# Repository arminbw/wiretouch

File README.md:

# WireTouch

WireTouch is an open multi-touch tracker based on mutual (projected) capacitance sensing. It was designed and built to foster research in the field of human-computer interaction. Please visit http://www.arminbwagner.com/wiretouch for demos and background information. You may also want to have a look at this paper:

.

The authors are currently not working on further updates. Feel free to fork the project and extend it as you see fit.

## Building
### WireTouch Firmware
1. The heart of the WireTouch hardware is an ATmega328P microcontroller equipped with an Arduino bootloader. To upload the WireTouch firmware, connect the mainboard with your computer. Use an USB to serial UART FTDI 5V cable.

2. Open **hardware/v1.3/firmware/firmware.ino** in the [Arduino IDE](http://arduino.cc/en/Main/Software). Select **Tools>Board>Arduino UNO** and the correct port. **Upload the Arduino sketch.**

Please note: The patched FTDI driver is not working in the latest version of OS X. Please skip step 3 and just use the default (and unfortunately slower) standard Apple FTDI driver. 

~~3. Install the virtual com port [FTDI driver](http://www.ftdichip.com/Drivers/VCP.htm). You need to patch the FTDIUSBSerialDriver configuration to increase the symbol rate of the computer-mainboard connection (see [FTDI Application Note 120](http://www.ftdichip.com/Support/Documents/AppNotes/AN_120_Aliasing_VCP_Baud_Rates.pdf)). We prepared a little perl script for that. Run it as the superuser: ```sudo perl modify-ftdi-driver-settings.pl``` If you are running El Capitan (or a later Mac OS version) you will also have to deactivate the new system integrity protection (SIP) to make this work \(see [issue #1](https://github.com/arminbw/wiretouch/issues/1)\).~~

### WireTouch Monitor
1. Download [openFrameworks 0.8.4](https://github.com/openframeworks/openFrameworks).
2. Download the following openFrameworks addons and put them into your openFrameworks ```addons``` directory:.

  * [ofxCv](https://github.com/kylemcdonald/ofxCv)
  * [ofxUI](https://github.com/rezaali/ofxUI)
  * [ofxBlobsManager](https://github.com/peteruithoven/ofxBlobsManager)

3. Copy the wiretouch_monitor directory of this repository into your openFrameworks ```apps/myApps/``` directory.
4. We are currently using Xcode 7.3 on OSX 10.11.4 for development. Open the Xcode project. **Build it**.

Next to the openFrameworks addons we are also using several other 3rd-party libraries. You do not have to download them manually as they already reside inside the src/3rd-party directory (This list is just for future reference and to give credit).
* [cjson](https://github.com/DaveGamble/cJSON)
* [oscpack](http://code.google.com/p/oscpack)
* [TUIO C++ library](https://github.com/mkalten/TUIO11_CPP)

## License
WireTouch is free software: you can redistribute it and/or modify it under the terms of the GNU General Public License as published by the Free Software Foundation, either version 3 of the License, or (at your option) any later version.

A few of the included 3rd-party libraries are licensed under the GPL-compatible MIT license.

WireTouch is distributed in the hope that it will be useful, but WITHOUT ANY WARRANTY; without even the implied warranty of merchantability or fitness for a particular purpose. See the [GNU General Public License](http://www.gnu.org/licenses) for more details.

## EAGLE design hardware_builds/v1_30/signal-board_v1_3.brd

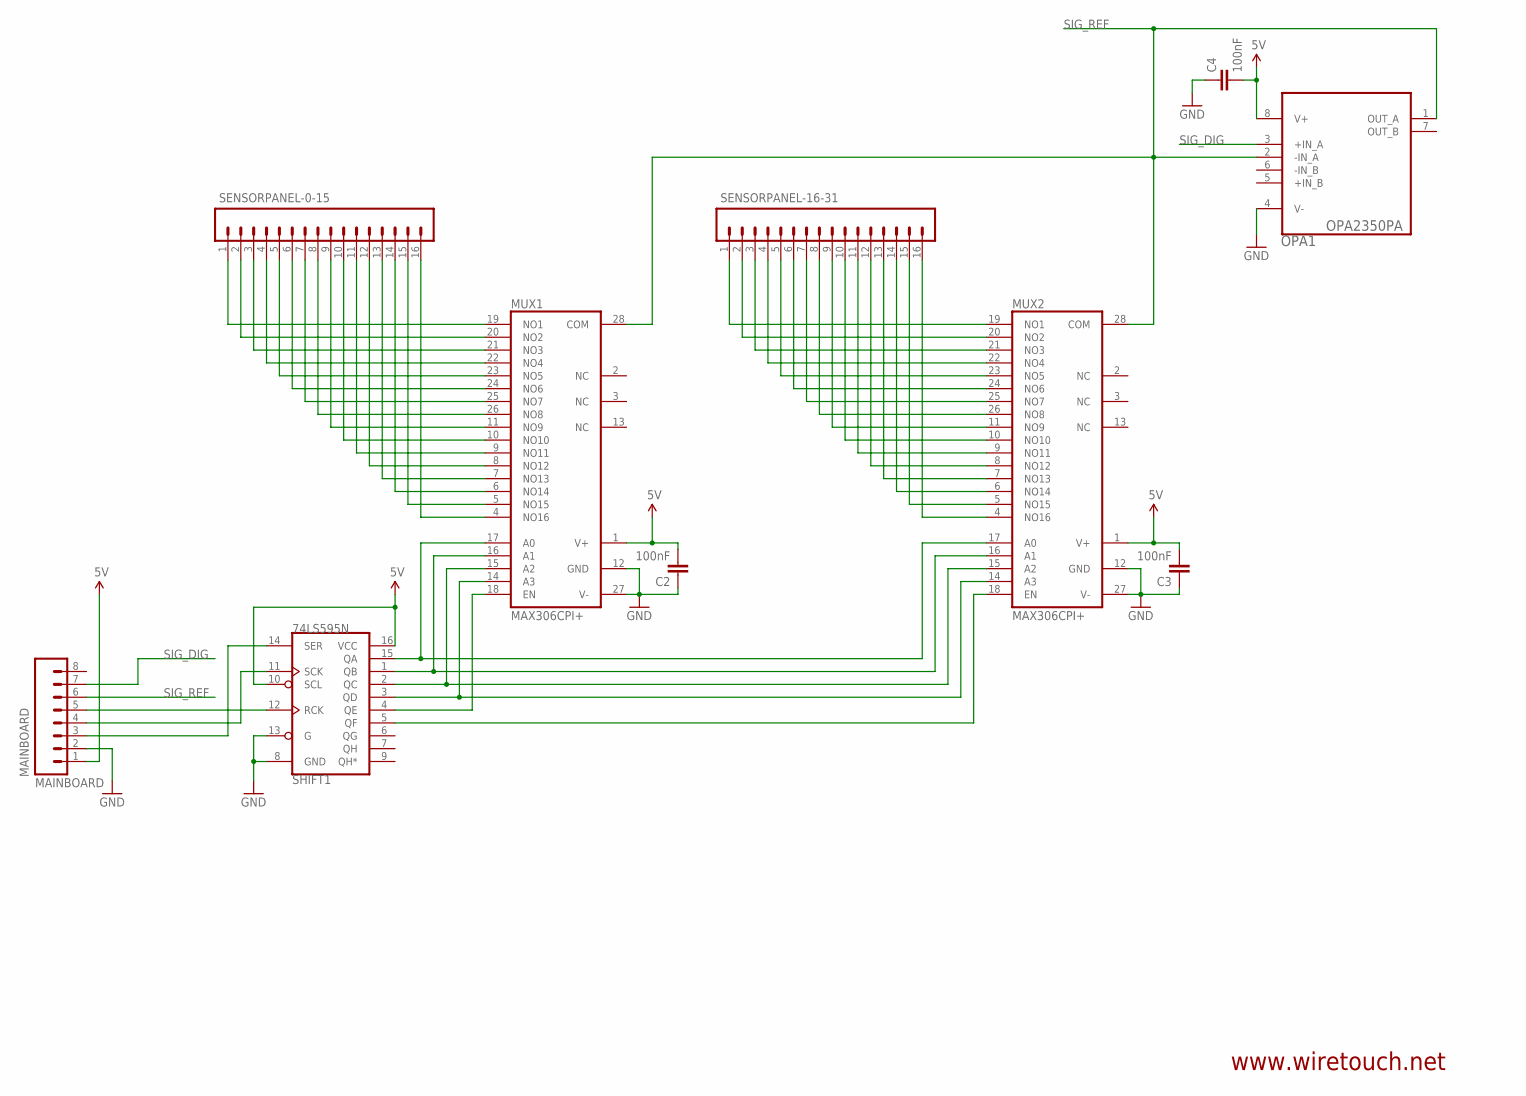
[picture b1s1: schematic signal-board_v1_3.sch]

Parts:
C2, C3, C4: 100nF; CAP-PTH-SMALL
MAINBOARD: MAINBOARD; 1X08_LONGPADS
MUX1, MUX2: MAX306CPI+; DIL28-6
OPA1: OPA2350PA; DIP254P762X508-8
SENSORPANEL-0-15, SENSORPANEL-16-31: M16LOCK_LONGPADS; 1X16_LOCK_LONGPADS
SHIFT1: 74LS595N; DIL16

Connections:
5V: C2.2, C3.2, C4.2, MAINBOARD.1, MUX1.1 (V+), MUX2.1 (V+), OPA1.8 (V+), SHIFT1.10 (SCL), SHIFT1.16 (VCC)
GND: C2.1, C3.1, C4.1, MAINBOARD.2, MUX1.12 (GND), MUX1.27 (V-), MUX2.12 (GND), MUX2.27 (V-), OPA1.4 (V-), SHIFT1.8 (GND), SHIFT1.13 (G)
unnamed: MUX1.19 (NO1), SENSORPANEL-0-15.1
unnamed: MUX1.21 (NO3), SENSORPANEL-0-15.3
unnamed: MUX1.23 (NO5), SENSORPANEL-0-15.5
unnamed: MUX1.25 (NO7), SENSORPANEL-0-15.7
unnamed: MUX1.11 (NO9), SENSORPANEL-0-15.9
unnamed: MUX1.9 (NO11), SENSORPANEL-0-15.11
unnamed: MUX1.7 (NO13), SENSORPANEL-0-15.13
unnamed: MUX1.5 (NO15), SENSORPANEL-0-15.15
unnamed: MUX2.19 (NO1), SENSORPANEL-16-31.1
unnamed: MUX2.21 (NO3), SENSORPANEL-16-31.3
unnamed: MUX2.23 (NO5), SENSORPANEL-16-31.5
unnamed: MUX2.25 (NO7), SENSORPANEL-16-31.7
unnamed: MUX2.11 (NO9), SENSORPANEL-16-31.9
unnamed: MUX2.9 (NO11), SENSORPANEL-16-31.11
unnamed: MUX2.7 (NO13), SENSORPANEL-16-31.13
unnamed: MUX2.5 (NO15), SENSORPANEL-16-31.15
unnamed: MUX1.20 (NO2), SENSORPANEL-0-15.2
unnamed: MUX1.22 (NO4), SENSORPANEL-0-15.4
unnamed: MUX1.24 (NO6), SENSORPANEL-0-15.6
unnamed: MUX1.26 (NO8), SENSORPANEL-0-15.8
unnamed: MUX1.10 (NO10), SENSORPANEL-0-15.10
unnamed: MUX1.8 (NO12), SENSORPANEL-0-15.12
unnamed: MUX1.6 (NO14), SENSORPANEL-0-15.14
unnamed: MUX1.4 (NO16), SENSORPANEL-0-15.16
unnamed: MUX2.20 (NO2), SENSORPANEL-16-31.2
unnamed: MUX1.16 (A1), MUX2.16 (A1), SHIFT1.1 (QB)
unnamed: MUX1.17 (A0), MUX2.17 (A0), SHIFT1.15 (QA)
unnamed: MUX1.15 (A2), MUX2.15 (A2), SHIFT1.2 (QC)
unnamed: MUX2.22 (NO4), SENSORPANEL-16-31.4
unnamed: MAINBOARD.3, SHIFT1.14 (SER)
unnamed: MUX1.18 (EN), SHIFT1.4 (QE)
unnamed: MUX2.18 (EN), SHIFT1.5 (QF)
unnamed: MAINBOARD.4, SHIFT1.11 (SCK)
unnamed: MUX1.14 (A3), MUX2.14 (A3), SHIFT1.3 (QD)
unnamed: MAINBOARD.5, SHIFT1.12 (RCK)
unnamed: MUX2.24 (NO6), SENSORPANEL-16-31.6
unnamed: MUX2.26 (NO8), SENSORPANEL-16-31.8
unnamed: MUX2.10 (NO10), SENSORPANEL-16-31.10
unnamed: MUX2.8 (NO12), SENSORPANEL-16-31.12
unnamed: MUX2.6 (NO14), SENSORPANEL-16-31.14
unnamed: MUX2.4 (NO16), SENSORPANEL-16-31.16
SIG_DIG: MAINBOARD.7, OPA1.3 (+IN_A)
SIG_REF: MAINBOARD.6, MUX1.28 (COM), MUX2.28 (COM), OPA1.1 (OUT_A), OPA1.2 (-IN_A)

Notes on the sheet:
www.wiretouch.net

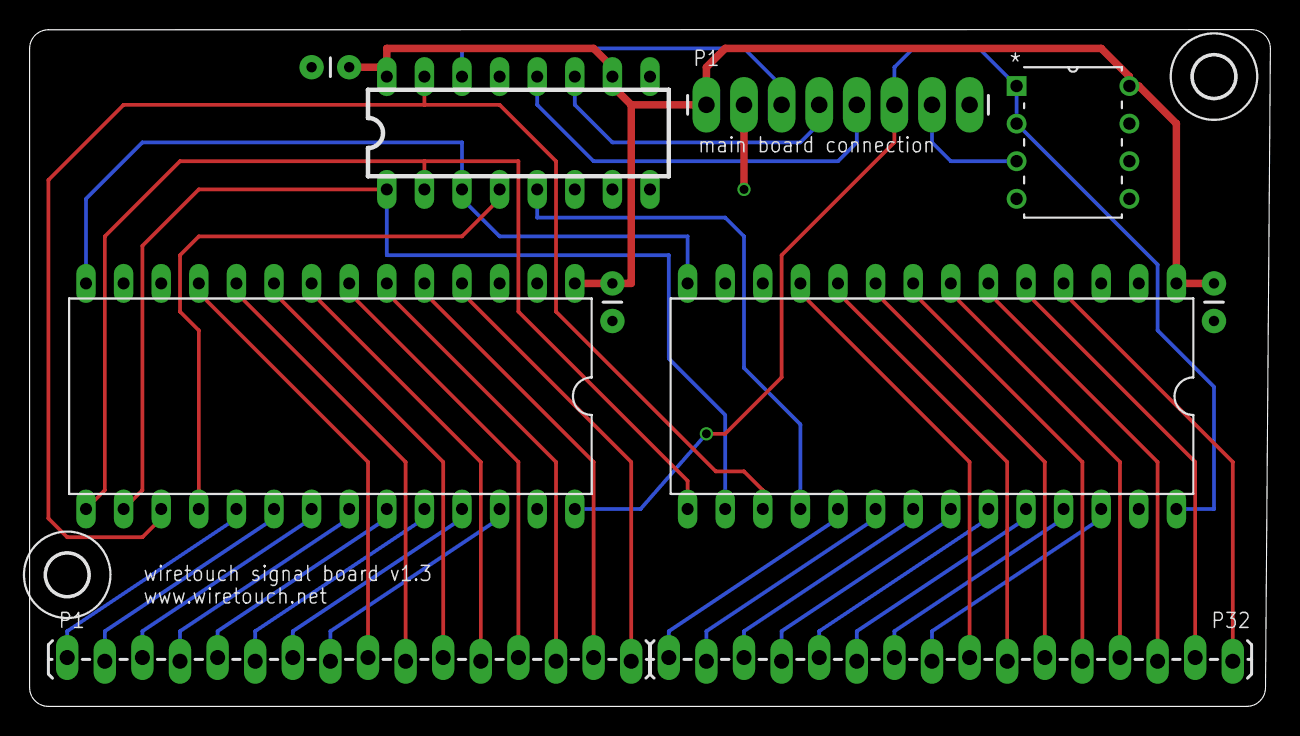
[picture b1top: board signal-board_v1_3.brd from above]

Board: 2 copper layers, 83.8 x 45.7 mm, 12 parts (0 on the bottom side), 45 nets.

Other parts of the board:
U$6, U$7: 2,8

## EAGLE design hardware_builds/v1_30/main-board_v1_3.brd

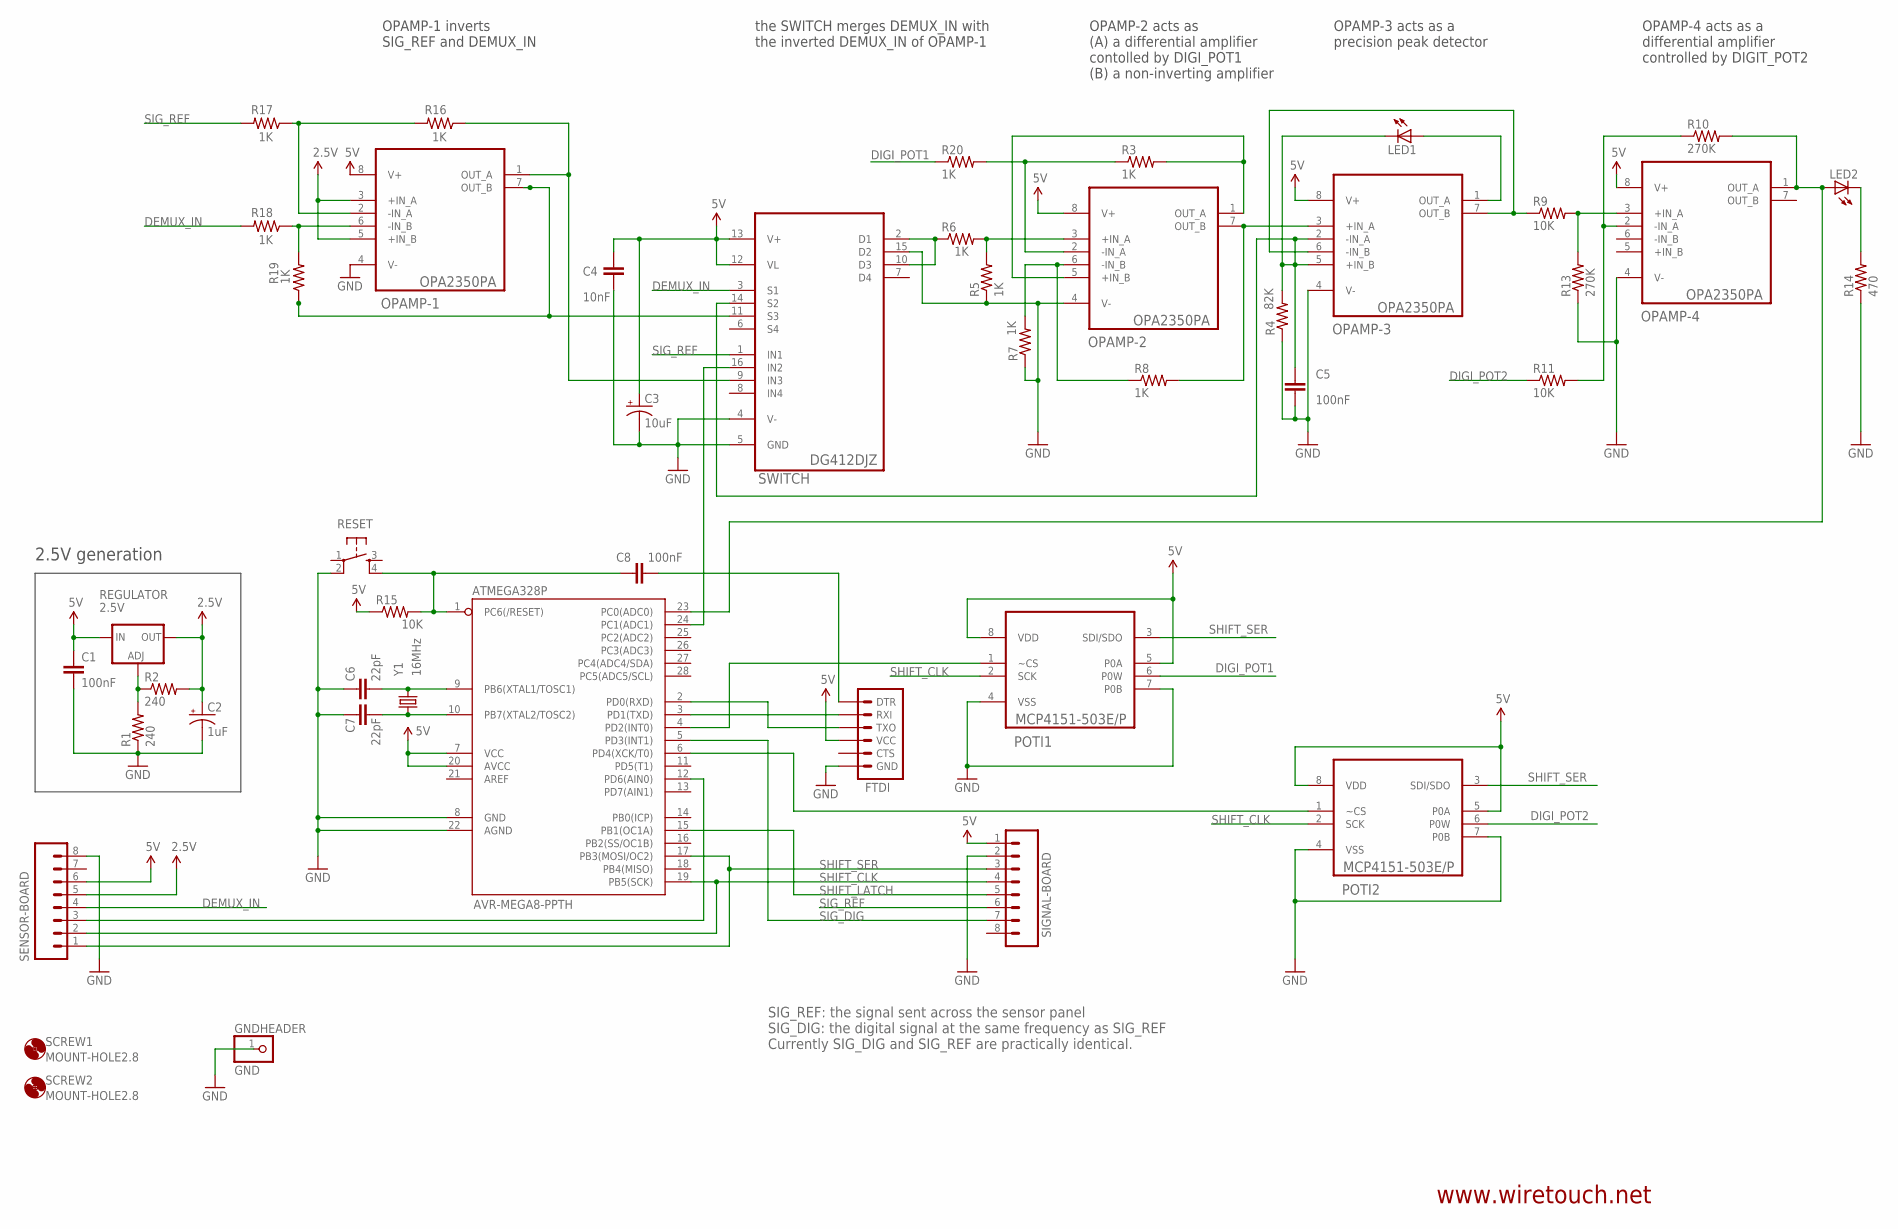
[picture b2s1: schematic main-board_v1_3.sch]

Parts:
ATMEGA328P: AVR-MEGA8-PPTH; DIL28-3
C1, C5: 100nF; CAP-PTH-SMALL
C2: 1uF; CPOL-RADIAL-10UF-25V
C3: 10uF; CPOL-RADIAL-10UF-25V
C4: 10nF; CAP-PTH-SMALL
C6, C7: 22pF; CAP-PTH-SMALL2
C8: 100nF; CAP-PTH-SMALL2
FTDI: ARDUINO_SERIAL_PROGRAMLONGPADS; 1X06_LONGPADS
GNDHEADER: GND; 1X01
LED1: LED3MM
LED2: LED5MM
OPAMP-1, OPAMP-2, OPAMP-3, OPAMP-4: OPA2350PA; DIP254P762X508-8
POTI1, POTI2: MCP4151-503E/P; DIP254P762X533-8
R1, R2: 240; AXIAL-0.3
R3, R5, R6, R7, R8, R16, R17, R18, R19, R20: 1K; AXIAL-0.3
R4: 82K; AXIAL-0.3
R9, R11, R15: 10K; AXIAL-0.3
R10, R13: 270K; AXIAL-0.3
R14: 470; AXIAL-0.3
REGULATOR: 2.5V; TO220-ADJ
RESET: Omron B3F momentary on switch; TACTILE-PTH
SCREW1, SCREW2: MOUNT-HOLE2.8; 2,8
SENSOR-BOARD: M08LONGPADS; 1X08_LONGPADS
SIGNAL-BOARD: M08LONGPADS; 1X08_LONGPADS
SWITCH: DG412DJZ; DIP254P762X533-16
Y1: 16MHz; HC49US

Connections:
2.8V: C2.1 (+), OPAMP-1.3 (+IN_A), OPAMP-1.5 (+IN_B), R2.P$2 (2), REGULATOR.OUT, SENSOR-BOARD.5
5V: ATMEGA328P.7 (VCC), ATMEGA328P.20 (AVCC), C1.1, C3.1 (+), C4.1, FTDI.4 (VCC), OPAMP-1.8 (V+), OPAMP-2.8 (V+), OPAMP-3.8 (V+), OPAMP-4.8 (V+), POTI1.5 (P0A), POTI1.8 (VDD), POTI2.5 (P0A), POTI2.8 (VDD), R15.P$1 (1), REGULATOR.IN, SENSOR-BOARD.6, SIGNAL-BOARD.1, SWITCH.12 (VL), SWITCH.13 (V+)
DEMUX_IN: R18.P$2 (2), SENSOR-BOARD.4, SWITCH.3 (S1)
DIGI_POT1: POTI1.6 (P0W), R20.P$1 (1)
DIGI_POT2: POTI2.6 (P0W), R11.P$1 (1)
GND: ATMEGA328P.8 (GND), ATMEGA328P.22 (AGND), C1.2, C2.2 (-), C3.2 (-), C4.2, C5.2, C6.1, C7.1, FTDI.6 (GND), GNDHEADER.1, OPAMP-1.4 (V-), OPAMP-2.4 (V-), OPAMP-3.4 (V-), OPAMP-4.4 (V-), POTI1.4 (VSS), POTI1.7 (P0B), POTI2.4 (VSS), POTI2.7 (P0B), R1.P$1 (1), R4.P$1 (1), R5.P$1 (1), R7.P$1 (1), R13.P$1 (1), R14.P$1 (1), RESET.2, SENSOR-BOARD.8, SIGNAL-BOARD.2, SWITCH.4 (V-), SWITCH.5 (GND), SWITCH.15 (D2)
unnamed: R6.P$1 (1), SWITCH.2 (D1), SWITCH.10 (D3)
unnamed: OPAMP-2.1 (OUT_A), OPAMP-2.5 (+IN_B), R3.P$2 (2)
unnamed: R1.P$2 (2), R2.P$1 (1), REGULATOR.ADJ
unnamed: OPAMP-2.2 (-IN_A), R3.P$1 (1), R20.P$2 (2)
unnamed: OPAMP-2.3 (+IN_A), R5.P$2 (2), R6.P$2 (2)
unnamed: OPAMP-2.6 (-IN_B), R7.P$2 (2), R8.P$1 (1)
unnamed: OPAMP-4.2 (-IN_A), R10.P$1 (1), R11.P$2 (2)
unnamed: ATMEGA328P.24 (PC1(ADC1)), SWITCH.16 (IN2)
unnamed: LED1.A, OPAMP-3.1 (OUT_A)
unnamed: OPAMP-2.7 (OUT_B), OPAMP-3.3 (+IN_A), R8.P$2 (2)
unnamed: C5.1, LED1.K (C), OPAMP-3.2 (-IN_A), OPAMP-3.5 (+IN_B), R4.P$2 (2), SWITCH.14 (S2)
unnamed: OPAMP-3.6 (-IN_B), OPAMP-3.7 (OUT_B), R9.P$1 (1)
unnamed: OPAMP-4.3 (+IN_A), R9.P$2 (2), R13.P$2 (2)
unnamed: ATMEGA328P.23 (PC0(ADC0)), LED2.A, OPAMP-4.1 (OUT_A), R10.P$2 (2)
unnamed: ATMEGA328P.6 (PD4(XCK/T0)), POTI2.1 (~CS)
unnamed: OPAMP-1.6 (-IN_B), R18.P$1 (1), R19.P$2 (2)
unnamed: LED2.K (C), R14.P$2 (2)
unnamed: ATMEGA328P.9 (PB6(XTAL1/TOSC1)), C6.2, Y1.2
unnamed: ATMEGA328P.10 (PB7(XTAL2/TOSC2)), C7.2, Y1.1
unnamed: ATMEGA328P.1 (PC6(/RESET)), C8.1, R15.P$2 (2), RESET.4
unnamed: ATMEGA328P.3 (PD1(TXD)), FTDI.2 (RXI)
unnamed: ATMEGA328P.2 (PD0(RXD)), FTDI.3 (TXO)
unnamed: C8.2, FTDI.1 (DTR)
unnamed: OPAMP-1.1 (OUT_A), R16.P$1 (1), SWITCH.9 (IN3)
unnamed: OPAMP-1.2 (-IN_A), R16.P$2 (2), R17.P$1 (1)
unnamed: OPAMP-1.7 (OUT_B), R19.P$1 (1), SWITCH.11 (S3)
unnamed: ATMEGA328P.4 (PD2(INT0)), POTI1.1 (~CS)
unnamed: ATMEGA328P.12 (PD6(AIN0)), SENSOR-BOARD.3
SHIFT_CLK: ATMEGA328P.19 (PB5(SCK)), POTI1.2 (SCK), POTI2.2 (SCK), SENSOR-BOARD.2, SIGNAL-BOARD.4
SHIFT_LATCH: ATMEGA328P.15 (PB1(OC1A)), SIGNAL-BOARD.5
SHIFT_SER: ATMEGA328P.17 (PB3(MOSI/OC2)), POTI1.3 (SDI/SDO), POTI2.3 (SDI/SDO), SENSOR-BOARD.1, SIGNAL-BOARD.3
SIG_DIG: ATMEGA328P.5 (PD3(INT1)), SIGNAL-BOARD.7
SIG_REF: R17.P$2 (2), SIGNAL-BOARD.6, SWITCH.1 (IN1)

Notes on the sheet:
2.5V generation
www.wiretouch.net
SIG_REF: the signal sent across the sensor panel SIG_DIG: the digital signal at the same frequency as SIG_REF Currently SIG_DIG and SIG_REF are practically identical.
OPAMP-3 acts as a precision peak detector
OPAMP-4 acts as a differential amplifier controlled by DIGIT_POT2
OPAMP-2 acts as (A) a differential amplifier contolled by DIGI_POT1 (B) a non-inverting amplifier
OPAMP-1 inverts SIG_REF and DEMUX_IN
the SWITCH merges DEMUX_IN with the inverted DEMUX_IN of OPAMP-1

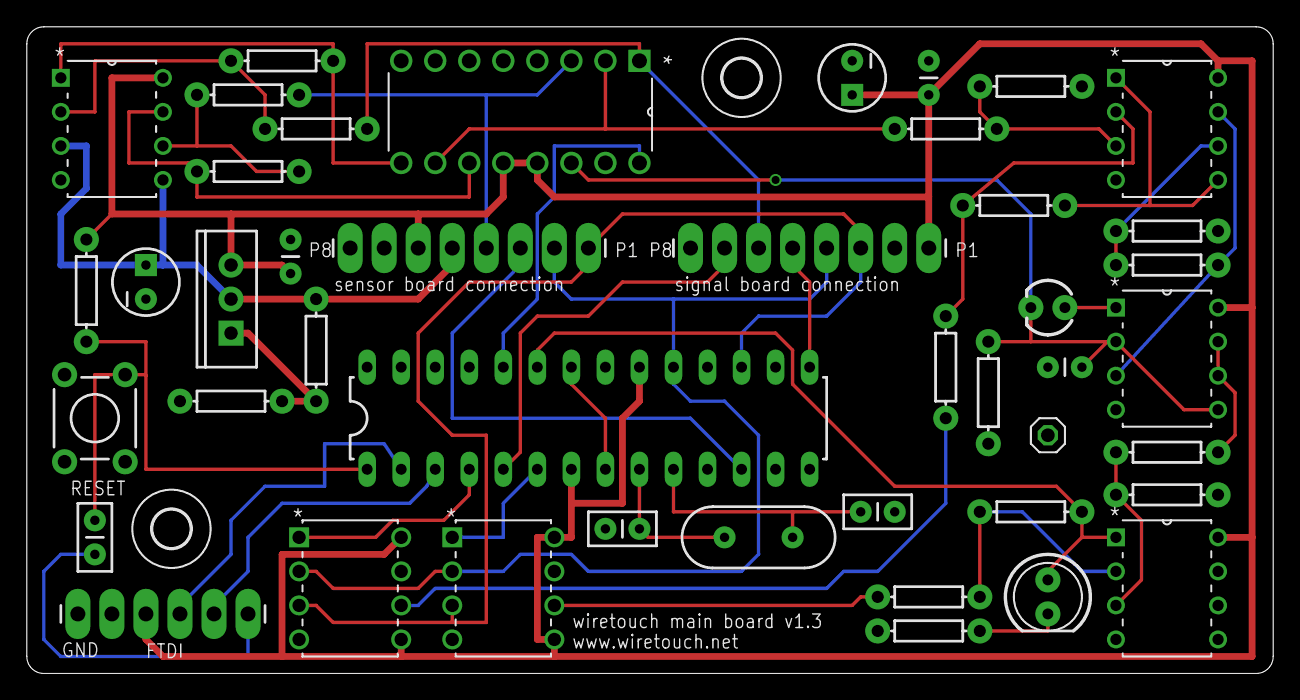
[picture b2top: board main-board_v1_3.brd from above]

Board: 2 copper layers, 93.0 x 48.3 mm, 46 parts (0 on the bottom side), 39 nets.

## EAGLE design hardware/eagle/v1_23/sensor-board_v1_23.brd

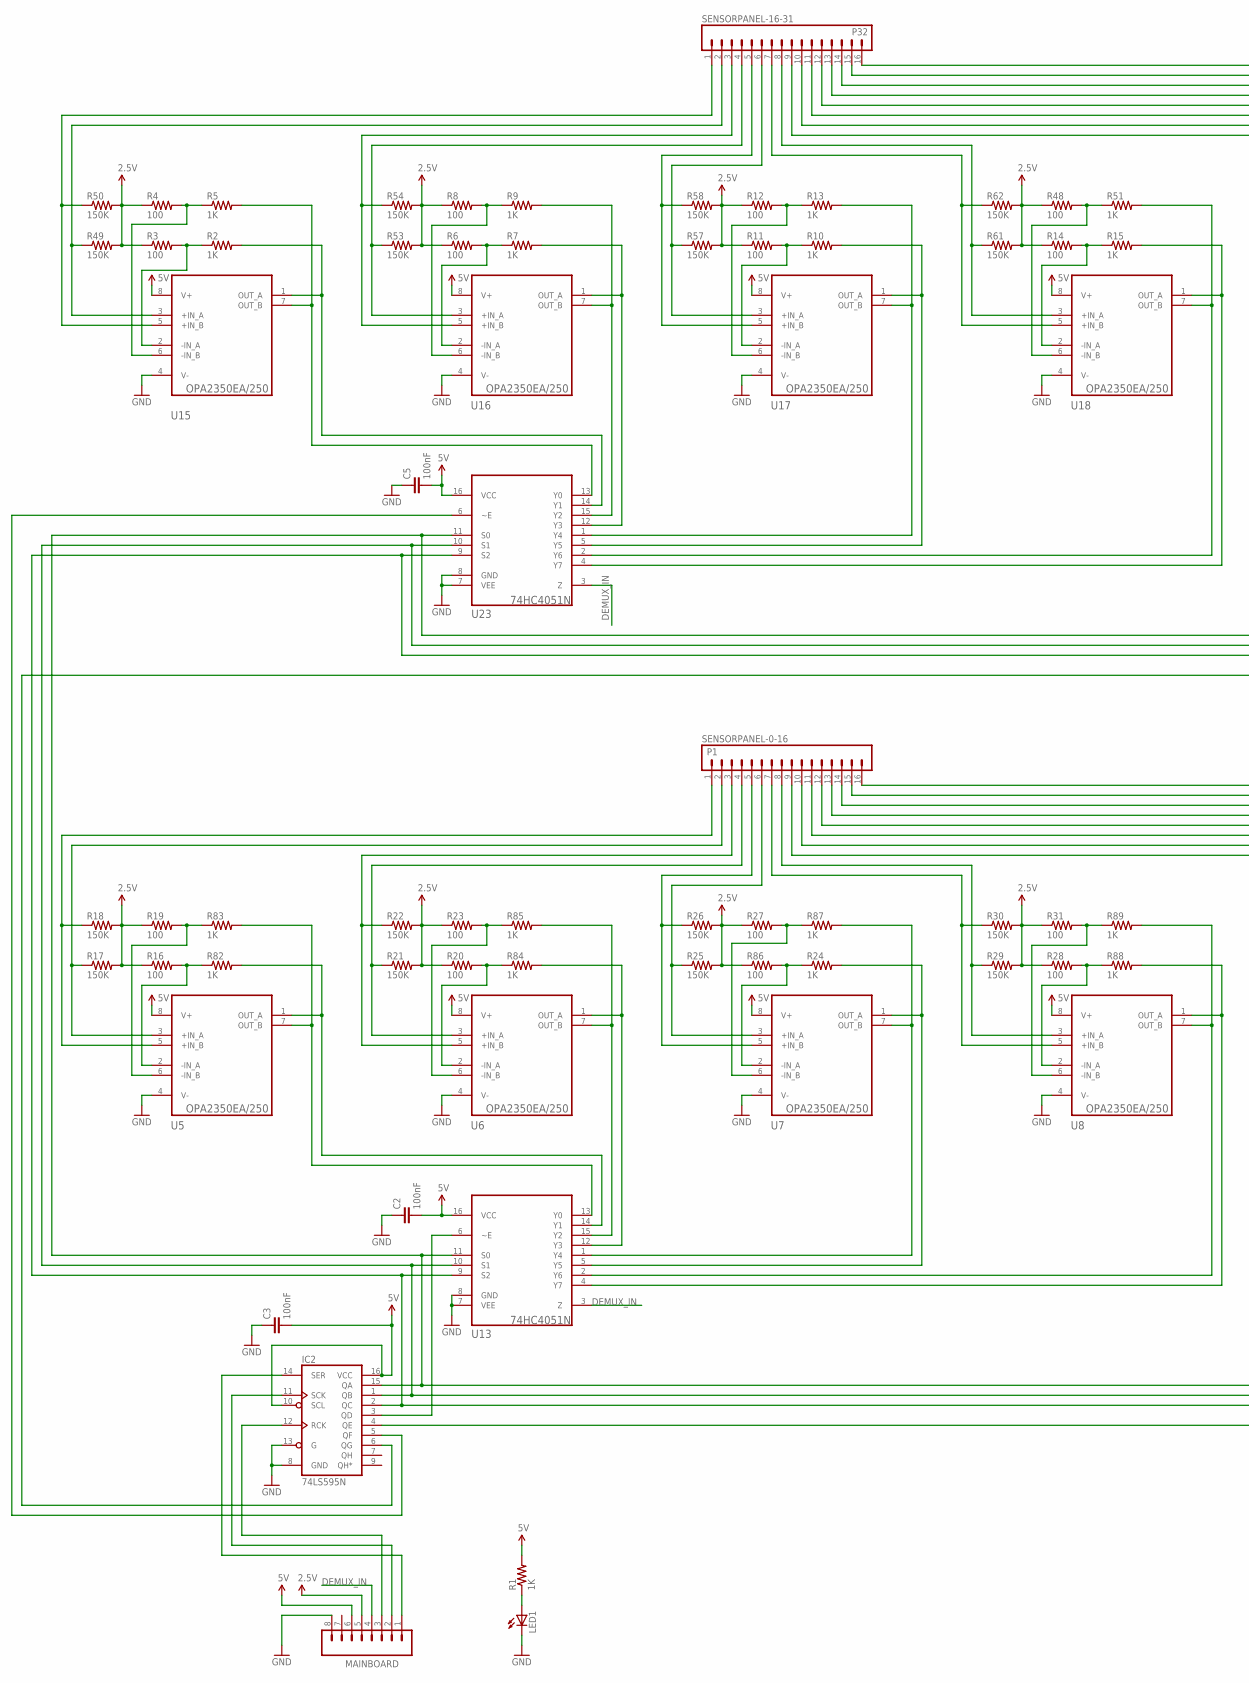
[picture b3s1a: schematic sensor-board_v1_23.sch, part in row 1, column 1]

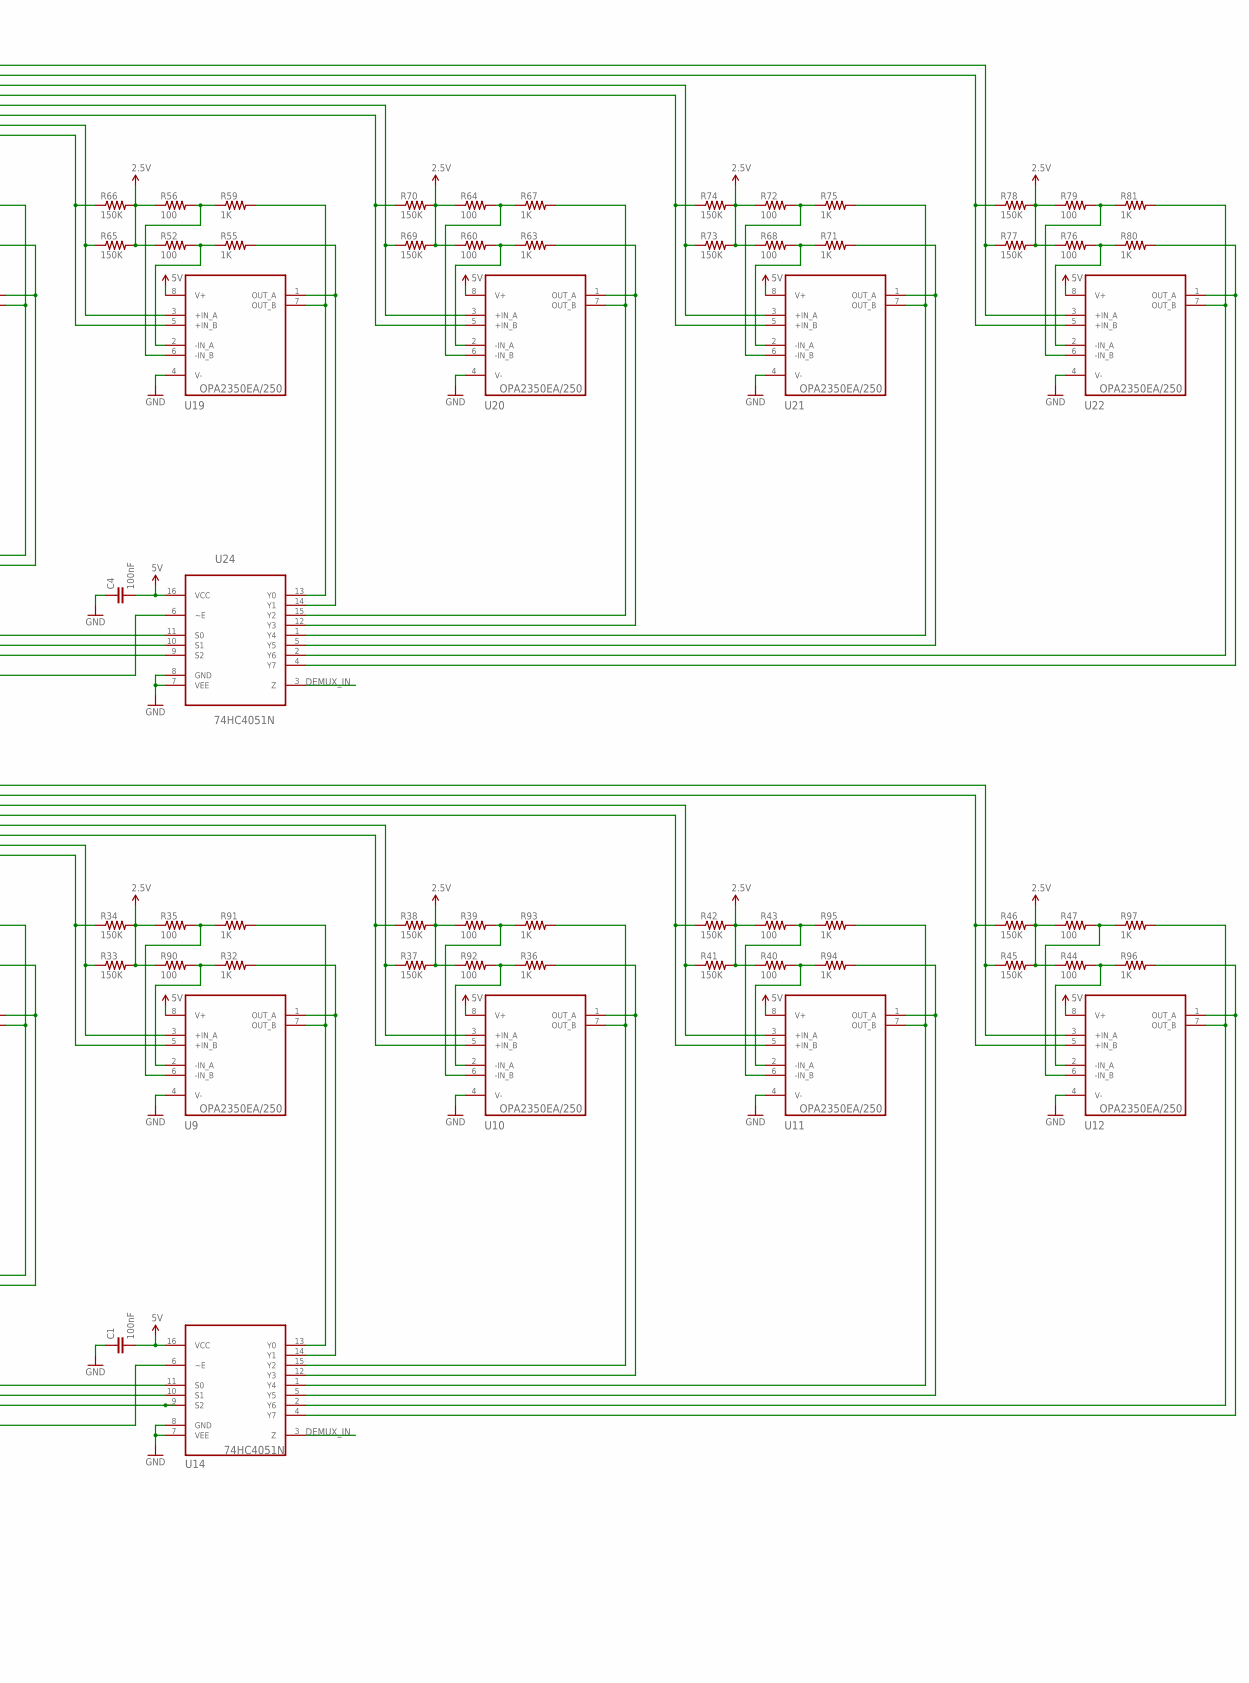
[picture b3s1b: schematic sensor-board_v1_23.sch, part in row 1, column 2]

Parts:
C1, C2, C3, C4, C5: 100nF; CAP-PTH-SMALL
IC2: 74LS595N; DIL16
LED1: LED0603; LED-0603
MAINBOARD: M08LONGPADS; 1X08_LONGPADS
R1, R2, R5, R7, R9, R10, R13, R15, R24, R32, R36, R51, R55, R59, R63, R67, R71, R75, R80, R81, R82, R83, R84, R85, R87, R88, R89, R91, R93, R94, R95, R96, R97: 1K; 0805
R3, R4, R6, R8, R11, R12, R14, R16, R19, R20, R23, R27, R28, R31, R35, R39, R40, R43, R44, R47, R48, R52, R56, R60, R64, R68, R72, R76, R79, R86, R90, R92: 100; 0805
R17, R18, R21, R22, R25, R26, R29, R30, R33, R34, R37, R38, R41, R42, R45, R46, R49, R50, R53, R54, R57, R58, R61, R62, R65, R66, R69, R70, R73, R74, R77, R78: 150K; 0805
SENSORPANEL-0-16: P1; 1X16_LOCK
SENSORPANEL-16-31: P32; 1X16_LOCK
U5, U6, U7, U8, U9, U10, U11, U12, U15, U16, U17, U18, U19, U20, U21, U22: OPA2350EA/250; SOP65P490X110-8N
U13, U14, U23, U24: 74HC4051N; DIP254P762X420-16

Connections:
2.8V: MAINBOARD.5, R3.1, R4.1, R6.1, R8.1, R11.1, R12.1, R14.1, R16.1, R17.2, R18.2, R19.1, R20.1, R21.2, R22.2, R23.1, R25.2, R26.2, R27.1, R28.1, R29.2, R30.2, R31.1, R33.2, R34.2, R35.1, R37.2, R38.2, R39.1, R40.1, R41.2, R42.2, R43.1, R44.1, R45.2, R46.2, R47.1, R48.1, R49.2, R50.2, R52.1, R53.2, R54.2, R56.1, R57.2, R58.2, R60.1, R61.2, R62.2, R64.1, R65.2, R66.2, R68.1, R69.2, R70.2, R72.1, R73.2, R74.2, R76.1, R77.2, R78.2, R79.1, R86.1, R90.1, R92.1
5V: C1.2, C2.2, C3.2, C4.2, C5.2, IC2.10 (SCL), IC2.16 (VCC), MAINBOARD.6, R1.2, U5.8 (V+), U6.8 (V+), U7.8 (V+), U8.8 (V+), U9.8 (V+), U10.8 (V+), U11.8 (V+), U12.8 (V+), U13.16 (VCC), U14.16 (VCC), U15.8 (V+), U16.8 (V+), U17.8 (V+), U18.8 (V+), U19.8 (V+), U20.8 (V+), U21.8 (V+), U22.8 (V+), U23.16 (VCC), U24.16 (VCC)
DEMUX_IN: MAINBOARD.4, U13.3 (Z), U14.3 (Z), U23.3 (Z), U24.3 (Z)
GND: C1.1, C2.1, C3.1, C4.1, C5.1, IC2.8 (GND), IC2.13 (G), LED1.C, MAINBOARD.8, U5.4 (V-), U6.4 (V-), U7.4 (V-), U8.4 (V-), U9.4 (V-), U10.4 (V-), U11.4 (V-), U12.4 (V-), U13.7 (VEE), U13.8 (GND), U14.7 (VEE), U14.8 (GND), U15.4 (V-), U16.4 (V-), U17.4 (V-), U18.4 (V-), U19.4 (V-), U20.4 (V-), U21.4 (V-), U22.4 (V-), U23.7 (VEE), U23.8 (GND), U24.7 (VEE), U24.8 (GND)
unnamed: LED1.A, R1.1
unnamed: R2.1, R3.2, U15.2 (-IN_A)
unnamed: R4.2, R5.1, U15.6 (-IN_B)
unnamed: R6.2, R7.1, U16.2 (-IN_A)
unnamed: R8.2, R9.1, U16.6 (-IN_B)
unnamed: R10.1, R11.2, U17.2 (-IN_A)
unnamed: R12.2, R13.1, U17.6 (-IN_B)
unnamed: R14.2, R15.1, U18.2 (-IN_A)
unnamed: R48.2, R51.1, U18.6 (-IN_B)
unnamed: R52.2, R55.1, U19.2 (-IN_A)
unnamed: R56.2, R59.1, U19.6 (-IN_B)
unnamed: R60.2, R63.1, U20.2 (-IN_A)
unnamed: R64.2, R67.1, U20.6 (-IN_B)
unnamed: R68.2, R71.1, U21.2 (-IN_A)
unnamed: R72.2, R75.1, U21.6 (-IN_B)
unnamed: R76.2, R80.1, U22.2 (-IN_A)
unnamed: R79.2, R81.1, U22.6 (-IN_B)
unnamed: R16.2, R82.1, U5.2 (-IN_A)
unnamed: R19.2, R83.1, U5.6 (-IN_B)
unnamed: R20.2, R84.1, U6.2 (-IN_A)
unnamed: R23.2, R85.1, U6.6 (-IN_B)
unnamed: R24.1, R86.2, U7.2 (-IN_A)
unnamed: R27.2, R87.1, U7.6 (-IN_B)
unnamed: R82.2, U5.1 (OUT_A), U13.14 (Y1)
unnamed: R83.2, U5.7 (OUT_B), U13.13 (Y0)
unnamed: R84.2, U6.1 (OUT_A), U13.12 (Y3)
unnamed: R28.2, R88.1, U8.2 (-IN_A)
unnamed: R17.1, SENSORPANEL-0-16.2, U5.3 (+IN_A)
unnamed: R18.1, SENSORPANEL-0-16.1, U5.5 (+IN_B)
unnamed: R31.2, R89.1, U8.6 (-IN_B)
unnamed: R85.2, U6.7 (OUT_B), U13.15 (Y2)
unnamed: R32.1, R90.2, U9.2 (-IN_A)
unnamed: R21.1, SENSORPANEL-0-16.4, U6.3 (+IN_A)
unnamed: R22.1, SENSORPANEL-0-16.3, U6.5 (+IN_B)
unnamed: R35.2, R91.1, U9.6 (-IN_B)
unnamed: R24.2, U7.1 (OUT_A), U13.5 (Y5)
unnamed: R87.2, U7.7 (OUT_B), U13.1 (Y4)
unnamed: R36.1, R92.2, U10.2 (-IN_A)
unnamed: R25.1, SENSORPANEL-0-16.6, U7.3 (+IN_A)
unnamed: R26.1, SENSORPANEL-0-16.5, U7.5 (+IN_B)
unnamed: R39.2, R93.1, U10.6 (-IN_B)
unnamed: R88.2, U8.1 (OUT_A), U13.4 (Y7)
unnamed: R89.2, U8.7 (OUT_B), U13.2 (Y6)
unnamed: R40.2, R94.1, U11.2 (-IN_A)
unnamed: R32.2, U9.1 (OUT_A), U14.14 (Y1)
unnamed: R30.1, SENSORPANEL-0-16.7, U8.5 (+IN_B)
unnamed: R44.2, R96.1, U12.2 (-IN_A)
unnamed: R29.1, SENSORPANEL-0-16.8, U8.3 (+IN_A)
unnamed: R91.2, U9.7 (OUT_B), U14.13 (Y0)
unnamed: R47.2, R97.1, U12.6 (-IN_B)
unnamed: R34.1, SENSORPANEL-0-16.9, U9.5 (+IN_B)
unnamed: R33.1, SENSORPANEL-0-16.10, U9.3 (+IN_A)
unnamed: R36.2, U10.1 (OUT_A), U14.12 (Y3)
unnamed: R93.2, U10.7 (OUT_B), U14.15 (Y2)
unnamed: R38.1, SENSORPANEL-0-16.11, U10.5 (+IN_B)
unnamed: R37.1, SENSORPANEL-0-16.12, U10.3 (+IN_A)
unnamed: R94.2, U11.1 (OUT_A), U14.5 (Y5)
unnamed: R95.2, U11.7 (OUT_B), U14.1 (Y4)
unnamed: R42.1, SENSORPANEL-0-16.13, U11.5 (+IN_B)
unnamed: R43.2, R95.1, U11.6 (-IN_B)
unnamed: R41.1, SENSORPANEL-0-16.14, U11.3 (+IN_A)
unnamed: R96.2, U12.1 (OUT_A), U14.4 (Y7)
unnamed: R97.2, U12.7 (OUT_B), U14.2 (Y6)
unnamed: R46.1, SENSORPANEL-0-16.15, U12.5 (+IN_B)
unnamed: R45.1, SENSORPANEL-0-16.16, U12.3 (+IN_A)
unnamed: R2.2, U15.1 (OUT_A), U23.14 (Y1)
unnamed: IC2.15 (QA), U13.11 (S0), U14.11 (S0), U23.11 (S0), U24.11 (S0)
unnamed: IC2.1 (QB), U13.10 (S1), U14.10 (S1), U23.10 (S1), U24.10 (S1)
unnamed: IC2.2 (QC), U13.9 (S2), U14.9 (S2), U23.9 (S2), U24.9 (S2)
unnamed: IC2.3 (QD), U13.6 (~E)
unnamed: IC2.4 (QE), U14.6 (~E)
unnamed: R5.2, U15.7 (OUT_B), U23.13 (Y0)
unnamed: R49.1, SENSORPANEL-16-31.2, U15.3 (+IN_A)
unnamed: R50.1, SENSORPANEL-16-31.1, U15.5 (+IN_B)
unnamed: R7.2, U16.1 (OUT_A), U23.12 (Y3)
unnamed: R9.2, U16.7 (OUT_B), U23.15 (Y2)
unnamed: R53.1, SENSORPANEL-16-31.4, U16.3 (+IN_A)
unnamed: R54.1, SENSORPANEL-16-31.3, U16.5 (+IN_B)
unnamed: R10.2, U17.1 (OUT_A), U23.5 (Y5)
unnamed: R13.2, U17.7 (OUT_B), U23.1 (Y4)
unnamed: R57.1, SENSORPANEL-16-31.6, U17.3 (+IN_A)
unnamed: R58.1, SENSORPANEL-16-31.5, U17.5 (+IN_B)
unnamed: R15.2, U18.1 (OUT_A), U23.4 (Y7)
unnamed: R51.2, U18.7 (OUT_B), U23.2 (Y6)
unnamed: R62.1, SENSORPANEL-16-31.7, U18.5 (+IN_B)
unnamed: R61.1, SENSORPANEL-16-31.8, U18.3 (+IN_A)
unnamed: R55.2, U19.1 (OUT_A), U24.14 (Y1)
unnamed: R59.2, U19.7 (OUT_B), U24.13 (Y0)
unnamed: R66.1, SENSORPANEL-16-31.9, U19.5 (+IN_B)
unnamed: R65.1, SENSORPANEL-16-31.10, U19.3 (+IN_A)
unnamed: R63.2, U20.1 (OUT_A), U24.12 (Y3)
unnamed: R67.2, U20.7 (OUT_B), U24.15 (Y2)
unnamed: R70.1, SENSORPANEL-16-31.11, U20.5 (+IN_B)
unnamed: R69.1, SENSORPANEL-16-31.12, U20.3 (+IN_A)
unnamed: R71.2, U21.1 (OUT_A), U24.5 (Y5)
unnamed: R75.2, U21.7 (OUT_B), U24.1 (Y4)
unnamed: R74.1, SENSORPANEL-16-31.13, U21.5 (+IN_B)
unnamed: R73.1, SENSORPANEL-16-31.14, U21.3 (+IN_A)
unnamed: R80.2, U22.1 (OUT_A), U24.4 (Y7)
unnamed: R81.2, U22.7 (OUT_B), U24.2 (Y6)
unnamed: R78.1, SENSORPANEL-16-31.15, U22.5 (+IN_B)
unnamed: R77.1, SENSORPANEL-16-31.16, U22.3 (+IN_A)
unnamed: IC2.5 (QF), U23.6 (~E)
unnamed: IC2.6 (QG), U24.6 (~E)
unnamed: IC2.12 (RCK), MAINBOARD.3
SHIFT_CLK: IC2.11 (SCK), MAINBOARD.2
SHIFT_SER: IC2.14 (SER), MAINBOARD.1

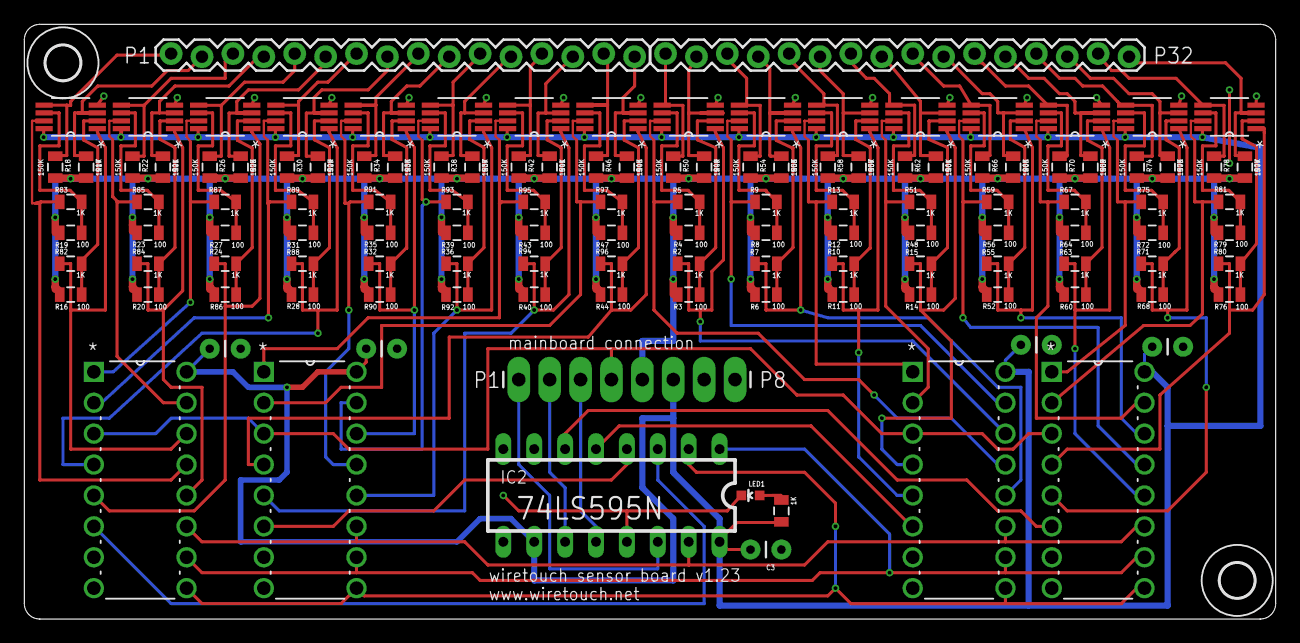
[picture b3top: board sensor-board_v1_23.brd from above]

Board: 2 copper layers, 102.9 x 48.9 mm, 129 parts (0 on the bottom side), 111 nets.

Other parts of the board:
U$1, U$2: 2,8

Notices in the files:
hardware_builds/v1_30/firmware/firmware.ino:
Copyright (C) 2011-2013 Georg Kaindl and Armin Wagner
parts and their libraries:
SparkFun-DigitalIC: Licensing: CC v3.0 Share-Alike You are welcome to use this library for commercial purposes.
SparkFun-Passives: Licensing: Creative Commons ShareAlike 4.0 International - https://creativecommons.org/licenses/by-sa/4.0
